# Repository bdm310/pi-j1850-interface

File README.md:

# pi-j1850-interface
A project to allow a RPi Zero W to communicate with the Chrysler J1850 bus.

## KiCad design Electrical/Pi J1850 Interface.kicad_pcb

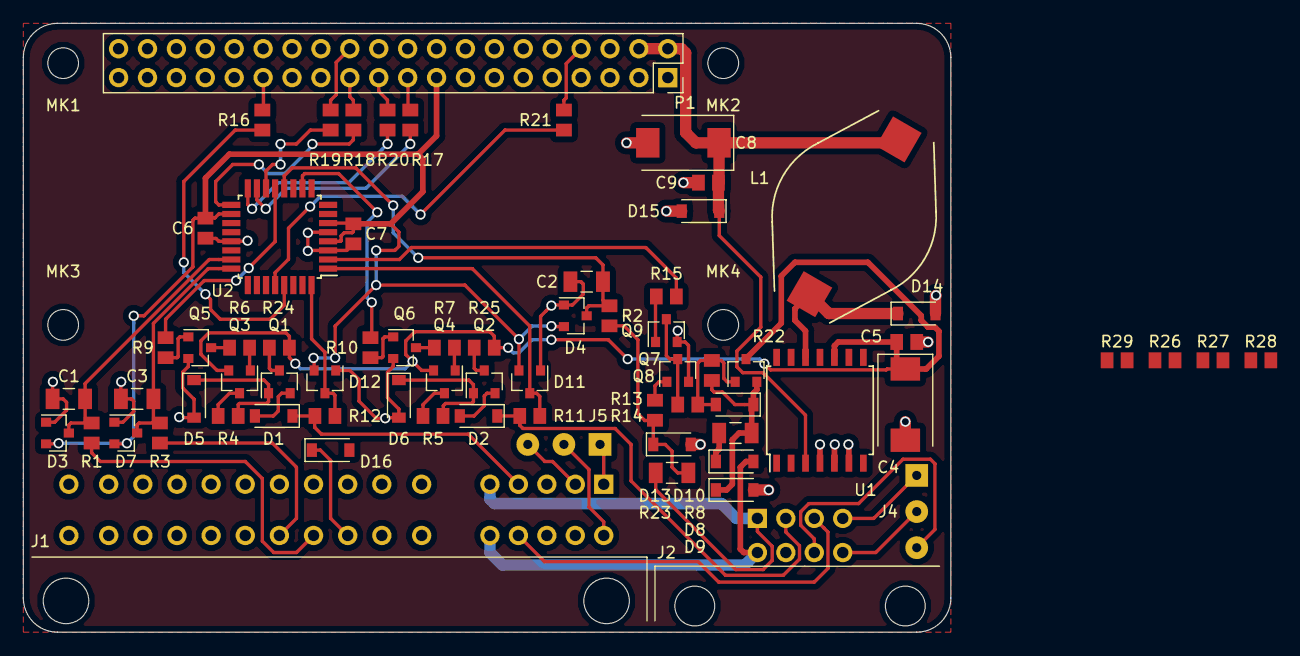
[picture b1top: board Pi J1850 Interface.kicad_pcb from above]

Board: 2 copper layers, 81.5 x 53.5 mm, 75 parts (0 on the bottom side), 60 nets.

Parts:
C1, C2, C3: 16n; C_1206_3216Metric
C4, C8: 47u; CP_EIA-7343-31_Kemet-D
C5, C9: 1u; C_0805_2012Metric
C6, C7: 100n; C_0805_2012Metric
D1, D2, D8, D14, D16: PMEG4010CEGWX; D_SOD-123
D3, D4, D7, D11, D12: BAS40-04; SOT-23
D5, D6, D10: 8V7; D_SOD-123
D9, D13: 20V; D_SOD-123
D15: 5V3; D_SOD-123
J1: TO ACCESSORIES; TE_MULTI-LOCK_ProprietaryChryslerRadio_2x5_and_2x11_P2.5mm_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
J2: FROM RADIO; TE_040-MULTI-LOCK_175973-4_2x04_P2.5mm_Horizontal
J4: LINE OUT; SolderWirePad_1x03_P3.175mm_Drill0.8mm
J5: LINE IN; SolderWirePad_1x03_P3.175mm_Drill0.8mm
L1: 470u; L_Bourns_SDR1806
MK1, MK2, MK3, MK4: M2.5; MountingHole_2.7mm_M2.5
P1: RASPBERRY PI; PinSocket_2x20_P2.54mm_Vertical
Q1, Q2, Q5, Q6, Q8, Q9: BC817; SOT-23
Q3, Q4: BC807; SOT-23
Q7: BSS83P; SOT-23
R1, R2, R3, R11, R12, R22, R26, R27, R28, R29: 100k; R_0805_2012Metric
R4, R5, R9, R10, R15, R16, R17, R18, R19, R20, R21: 1k; R_0805_2012Metric
R6, R7, R13, R14: 10k; R_0805_2012Metric
R8, R23: 4R7; R_1206_3216Metric
R24, R25: 100R; R_0805_2012Metric
U1: LM2574M-5; SOIC-14W_7.5x9.0mm_P1.27mm
U2: ATmega328P-AU; TQFP-32_7x7mm_P0.8mm

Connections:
+3V3: C6.1, C7.1, D3.2, D4.2, D7.2, D11.2, D12.2, P1.17, U2.4, U2.6, U2.18
+5V: C8.1, C9.1, D15.1, L1.2, P1.2, P1.4, U1.3
+12V: C4.1, C5.1, Q3.2, Q4.2, Q7.3, R24.2, R25.2, U1.10
/+SW: D16.1, J1.24
/ACC: J1.5, J2.1, R23.2
/ACC_B: Q8.1, R14.1, R26.2
/ACC_FLT: C2.1, D4.3, R2.1, U2.12
/ACC_PROT: D13.1, R2.2, R14.2, R23.1
/AUDIO_GND_IN: J1.2, J5.3
/AUDIO_GND_OUT: J2.7, J4.3
/AUDIO_L_IN: J1.17, J5.2
/AUDIO_L_OUT: J2.8, J4.2
/AUDIO_R_IN: J1.1, J5.1
/AUDIO_R_OUT: J2.4, J4.1
/BATT: D8.2, J1.21, J2.5
/BATT+: D8.1, R8.2
/BATT_EN: Q8.3, Q9.3, R13.1
/BATT_EN_GATE: D10.2, Q7.1, R13.2, R22.1
/BATT_PROT: D9.1, D10.1, Q7.2, R8.1, R22.2
/GPIO5: P1.29, R16.1
/GPIO5_R: R16.2, U2.29
/GPIO8(SPI0_CE_N): P1.24, R19.1
/GPIO8(SPI0_CE_N)_R: R19.2, U2.14
/GPIO9(SPI0_MISO): P1.21, R20.1
/GPIO9(SPI0_MISO)_R: R20.2, U2.16
/GPIO10(SPI0_MOSI): P1.19, R17.1
/GPIO10(SPI0_MOSI)_R: R17.2, U2.15
/GPIO11(SPI0_SCK): P1.23, R18.1
/GPIO11(SPI0_SCK)_R: R18.2, U2.17
/GPIO14(TXD0): P1.8, R21.1
/GPIO14(TXD0)_R: R21.2, U2.28
/J1850_IN: D1.1, J1.4, R12.2
/J1850_IN_CMD: R9.1, U2.13
/J1850_IN_CMD_B: Q5.1, R9.2, R28.2
/J1850_IN_CMD_B1: Q3.1, R6.2
/J1850_IN_CMD_B1_R: Q5.3, R6.1
/J1850_IN_CMD_B2: D5.1, Q1.1, R4.1
/J1850_IN_CMD_B2_R: Q3.3, R4.2
/J1850_IN_D: D1.2, Q1.2
/J1850_IN_FLT: D12.3, R12.1, U2.32
/J1850_IN_R: Q1.3, R24.1
/J1850_OUT: D2.1, J2.2, R11.2
/J1850_OUT_CMD: R10.1, U2.10
/J1850_OUT_CMD_B: Q6.1, R10.2, R29.2
/J1850_OUT_CMD_B1: Q4.1, R7.2
/J1850_OUT_CMD_B1_R: Q6.3, R7.1
/J1850_OUT_CMD_B2: D6.1, Q2.1, R5.1
/J1850_OUT_CMD_B2_R: Q4.3, R5.2
/J1850_OUT_D: D2.2, Q2.2
/J1850_OUT_FLT: D11.3, R11.1, U2.1
/J1850_OUT_R: Q2.3, R25.1
/PWD: J1.20, J2.3
/PWR_HOLD: R15.1, U2.2
/PWR_HOLD_B: Q9.1, R15.2, R27.2
/SW: D14.1, L1.1, U1.12
/SW1: J1.25, R1.2
/SW1_FLT: C1.1, D3.3, R1.1, U2.23
/SW2: J1.26, R3.2
/SW2_FLT: C3.1, D7.3, R3.1, U2.24
GND: C1.2, C2.2, C3.2, C4.2, C5.2, C6.2, C7.2, C8.2, C9.2, D3.1, D4.1, D5.2, D6.2, D7.1, D9.2, D11.1, D12.1, D13.2, D14.2, D15.2, J1.3, J1.18, J2.6, P1.6, P1.9, P1.14, P1.20, P1.25, P1.30, P1.34, P1.39, Q5.2, Q6.2, Q8.2, Q9.2, R26.1, R27.1, R28.1, R29.1, U1.4, U1.5, U1.6, U2.3, U2.5, U2.21

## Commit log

2018-05-18 Rev - inital commit of electrical design files
2018-05-18 Updated schematic to reflect added pull downs for some transistors. Added mechanical model.
2018-05-18 Added readme and license.
2018-06-02 Initial semi-working J1850 and power control code
2018-06-05 Commit before removing second J1850 bus
2018-06-15 Better working dual J1850 busses, prelim sat masquerade and comms notes
2018-06-17 Added pi side daemon to vcs, minor changes to firmware
2018-06-18 Added switches, kind of
2018-06-20 Big rewrite resulting in functional steering wheel controls, track display, and bluetooth player controls
2018-10-03 Added logic to search for bluetooth player object
2018-10-03 Modified device search to account for multiple paired devices
